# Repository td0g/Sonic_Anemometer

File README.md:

# Sonic_Anemometer

## License

Documentation is licensed under a [Creative Commons Attribution 4.0 International License](https://creativecommons.org/licenses/by/4.0/)

Software is licensed under a [GNU GPL v3 License](https://www.gnu.org/licenses/gpl-3.0.txt)

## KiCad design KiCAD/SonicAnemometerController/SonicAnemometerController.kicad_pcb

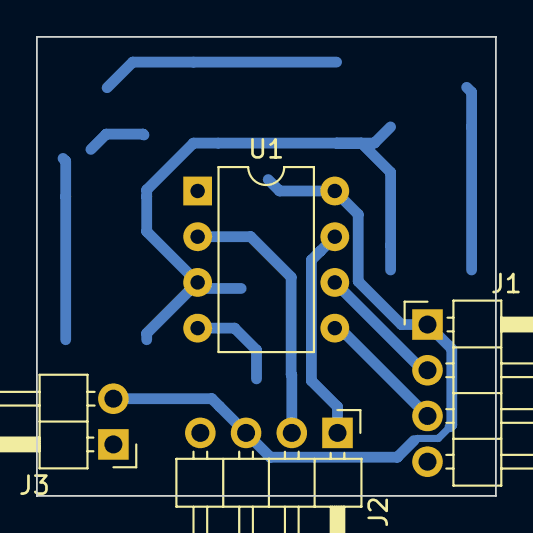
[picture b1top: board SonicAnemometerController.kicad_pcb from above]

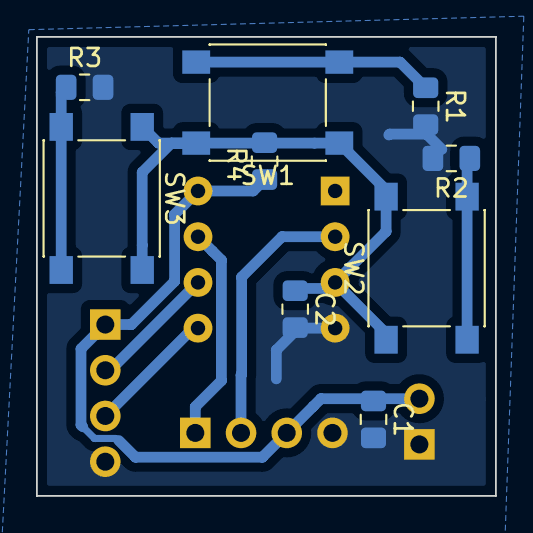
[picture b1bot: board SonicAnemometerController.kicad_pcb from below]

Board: 2 copper layers, 25.5 x 25.5 mm, 13 parts (9 on the bottom side), 10 nets.

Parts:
C1, C2: C; C_0805_2012Metric_Pad1.15x1.40mm_HandSolder
J1, J2: Conn_01x04; PinHeader_1x04_P2.54mm_Horizontal
J3: Conn_01x02; PinHeader_1x02_P2.54mm_Horizontal
R1, R2, R3, R4: R; R_0805_2012Metric_Pad1.15x1.40mm_HandSolder
SW1, SW2, SW3: SW_Push; SW_Push_1P1T_NO_6x6mm_H9.5mm
U1: ATtiny85-20PU; DIP-8_W7.62mm

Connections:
GND: C1.2, C2.2, J1.4, J2.4, J3.1, R1.2, R2.2, R3.2, U1.4
unnamed: C2.1, R4.2, SW1.1, SW2.1, SW3.1, U1.3
unnamed: J1.2, U1.6
unnamed: J1.3, U1.5
unnamed: J2.1, U1.7
unnamed: J2.2, U1.2
unnamed: R1.1, SW1.2
unnamed: R2.1, SW2.2
unnamed: R3.1, SW3.2
VCC: C1.1, J1.1, J2.3, J3.2, R4.1, U1.8
